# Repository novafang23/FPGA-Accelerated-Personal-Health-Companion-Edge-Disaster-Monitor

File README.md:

# SIH26181: VALOR (Vital and Atmospheric Logic for Offline Rescue)
### FPGA-Accelerated Personal Health Companion & Edge Disaster Monitor

An end-to-end heterogeneous edge System-on-Chip (SoC) pairing **synthesizable Verilog hardware acceleration** (Renesas ForgeFPGA & Xilinx Zynq-7000) with **dual-core ESP32-S3 FreeRTOS firmware** and an **on-device INT8 TinyML neural network**. Designed to operate 100% offline in communication-denied disaster environments, it delivers 20 ns cycle-accurate PPG jitter elimination, real-time mNEWS2 clinical triage, and multi-hazard environmental risk assessment (heatwaves, toxic smog, and floods).

---

## 🏷️ Platform Status & Roadmap

* **Verified Baseline:** [Xilinx Zynq-7000 (`xc7z020`)](hardware/zynq/) — Fully verified with 6/6 passing self-checking tests and static timing closed at 69.45 MHz (permanently tagged at `v1.0-zynq-SIH`).
* **Active Port:** [ShrikeFi (ESP32-S3 + Renesas ForgeFPGA)](hardware/shrikefi/) — Affordable edge hardware platform. Post-synthesis fitter reports **533 / 1120 LUT5s (47.59%)**, 367 FFs and 118/140 CLBs (84.29%) at **Fmax 77.712 MHz, WNS +7.131 ns** against the 50 MHz clock, with 13 passing self-checking link checks (5 groups). Raw synthesis logs: [`hardware/shrikefi/synthesis_evidence/`](hardware/shrikefi/synthesis_evidence/) (read its README — two older, superseded builds' numbers are also in there). Includes **fully integrated ESP32-S3 firmware** that streams live health telemetry via **USB UART & WiFi/MQTT**. (The firmware also programs the FPGA over **SPI2** at every boot using the Vicharak `Web_FPGA_programmer.ino` sequence; the boot log reaches `configuration COMPLETE! (46408 bytes loaded)` and the runtime link then answers its `0x55` probe, which is the real proof a configured design is running. See [`firmware/shrikefi/README.md`](firmware/shrikefi/README.md#fpga-delivery-how-the-bitstream-reaches-the-fpga).)
* **Clinical Intelligence & Biomarkers:** Fuses **mNEWS2 Clinical Triage (Royal College of Physicians)**, **PPG-derived Respiratory Rate (Charlton 2018)**, **Signal Quality Index (Elgendi 2016 skewness + project perfusion/IBI terms)**, **Moran's Physiological Strain Index (PSI)**, **PM2.5-HRV autonomic-strain heuristic (motivated by Brook et al. 2010)**, and the **published PMS5003 PM2.5 correction** (EPA/Barkjohn 2021 method, AirGradient's PMS5003 atm-channel equations) applied to a 60 s rolling mean.
* **Interactive Graphical Dashboard:** Standalone Windows desktop GUI (`shrikefi_dashboard.exe`) featuring a 60 FPS real-time optical PPG oscilloscope, live vital displays, and dual-mode operation (Live Hardware streaming + 6 simulated disaster profiles).

---

## 🔬 Reproducibility & Evidence Provenance

Every headline number below is reproducible from a committed command. Where a claim **cannot** be fully reproduced from this repository, that is stated explicitly rather than glossed over.

### Reproducible claims

| Claim | Reproduce with | Expected result |
|---|---|---|
| Zynq RTL — self-checking testbench | `hardware/zynq/build_and_run.bat` (or the `iverilog`/`vvp` pair it wraps) | `6 passed, 0 failed` |
| ShrikeFi RTL — SPI link testbench (`hardware/shrikefi/tb_forgefpga_system.v`) | `hardware/shrikefi/build_shrikefi_sim.bat` | `RESULTS: 13 passed, 0 failed (out of 13 checks)` |
| Firmware unit tests (incl. FP32↔INT8 parity) | `make -C firmware/zynq test` | `ALL TESTS PASSED.` |
| INT8 model regeneration | `python3 firmware/core/train_nn_risk_model.py` | `88.47%` FP32 / `88.39%` INT8 teacher agreement, `619` params, INT8 max error `0.091` |
| Clinical triage metrics | build & run `firmware/core/accuracy_evaluator.c` on `data/mimic/mimic_eval_feed.csv` | sensitivity `58.18%`, specificity `98.19%` (accuracy `94.11%`), TP `971` / FP `267` / TN `14451` / FN `698` |
| MIMIC cohort scan | build & run `firmware/core/mimic_harness.c` on `data/mimic/mimic_vital_feed.csv` | 16,387 records over 98 subjects |
| Zynq resource/timing reports | `hardware/zynq/synthesis_evidence/*.rpt` | see that directory's README |
| ForgeFPGA resource report | `hardware/shrikefi/synthesis_evidence/resource_utilization_spi_link_crest_2026-11-02.log` | 533/1120 LUT5s, 367 FFs, 118/140 CLBs (see that directory's README) |

CI (`.github/workflows/ci.yml`) runs the Zynq testbench, the ShrikeFi testbench, the firmware unit tests, and the accuracy evaluator, and fails the build if the model drops below its accuracy floor.

### Provenance caveats — read before quoting these numbers

1. **The RMSSD column in the MIMIC feeds is synthetic.** The HR and SpO₂ columns are genuine MIMIC-III `CHARTEVENTS` values (verified against the raw tables — e.g. subject 10013: SpO₂ min 60, HR max 113, 82 rows, matching the feed exactly). But **MIMIC-III v1.4 contains no waveform, ECG or numerics tables**, so beat-to-beat intervals — and therefore RMSSD — cannot be derived from it. The feed's RMSSD is generated: it has 16,384 distinct values across 16,387 rows over only 1,433 distinct (HR, SpO₂) pairs, i.e. essentially a unique float per row. Treat any metric that depends on RMSSD as *conditional on that synthetic input*.
2. **The dataset is the MIMIC-III demo subset** (98 subjects), not the full MIMIC-III cohort. It is a benchmark fixture, not an epidemiological result.
3. **`ground_truth_crisis` is derived in-tree.** No upstream generator script for those labels is committed, and the labels vary within a patient over time, consistent with a vitals-derived rule. The triage metrics are therefore best read as *agreement with that labeling rule*, not as independent clinical validation.
4. **The "88.39% accuracy" figure is agreement with a rule-based teacher**, not with clinical outcomes. `train_nn_risk_model.py` distils `disaster_risk_engine.c` into a 619-parameter network; both the training labels and the validation labels come from that same teacher.
5. **The 185 LUT / +5.603 ns Zynq figures are the tagged `v1.0-zynq-SIH` baseline.** Their only surviving in-repo evidence is the PNG screenshots; the raw report was overwritten when `.runs/` was regenerated under Vivado 2026.1. See [`hardware/zynq/synthesis_evidence/README.md`](hardware/zynq/synthesis_evidence/README.md) for which numbers belong to which run.
6. **ESP32-S3 inference latency is not measured.** The `0.44 µs` figure is an x86-64 host measurement. Do not quote it as a target-device number.

---

## 📌 Key Architectural Highlights

* **Cycle-Accurate Hardware Timing:** Dedicated 50 MHz FPGA timer measures heartbeat Inter-Beat Intervals (IBI) with **20 nanoseconds resolution**, eliminating the 5–20 ms operating system scheduling jitter that corrupts Heart Rate Variability (HRV).
* **Area-Optimized DSP Architecture:** Single 8-tap moving average filter implemented using an **$O(1)$ running-sum algorithm with wire-shift division (`>> 3`)**, requiring **0 DSP48 multiplier slices and 0 Block RAMs**.
* **Robust Bus Interfacing:** Standard ARM AMBA AXI4-Lite slave engine with **decoupled `AW` and `W` channel handshakes**, eliminating bus deadlocks on out-of-order interconnects. Includes **Write-1-to-Clear (W1C)** status registers to prevent interrupt race conditions.
* **High-Accuracy On-Device TinyML (INT8):** 2-hidden-layer micro-architecture ($6 \to 24 \to 16 \to 3$) requiring only **619 bytes** of parameter storage, reaching **88.39% agreement with the rule engine** on a 7,000-sample held-out synthetic validation set (88.47% for the float32 reference) (see [Reproducibility](#-reproducibility--evidence-provenance)) with **97.32% FP32↔INT8 tier agreement**, and executing in **0.44 µs per inference** (measured, `-O2`, x86-64 host; ESP32-S3 target timing not yet measured) with zero cloud dependencies.
* **Multi-Disaster Resilience (Tailored for India):**
  * *Heat Waves:* Fuses **NOAA Steadman Heat Index** and **Moran's Physiological Strain Index (PSI)** with cardiac tachycardia to warn of heat exhaustion before collapse.
  * *Smog Events:* Combines **published-correction PM2.5** (EPA/AirGradient banded equations on a 60 s mean, with a confidence code) with an **AHA-motivated PM2.5-HRV autonomic-strain heuristic** to flag acute vagal suppression ($RMSSD$ drop).
  * *Floods / Cold Shock:* Detects rapid skin cooling, cold-shock hyperventilation, and bradycardia.
* **Qualcomm Silicon Portability:** Prototyped on Xilinx Zynq-7000 and Renesas ForgeFPGA with a defined production migration roadmap to **Qualcomm Snapdragon Wear W5+ Gen 1** using **Hexagon™ Vector eXtensions (HVX)** on the Low-Power Island (< 5 mW) and **Qualcomm AI Engine (SNPE/QNN)**.

---

## 🏛️ System Architecture & End-to-End Data Flow

### 1. High-Level Dataflow Pipeline
The system operates across four coordinated processing tiers, moving from raw physical sensor acquisition to hardware-accelerated DSP, on-device TinyML inference, and local offline hazard advisory:

### 2. Heterogeneous Hardware / Firmware Architecture

```
┌──────────────────────────────────────────────────────────────────────────────────────────────────────┐
│                                       PHYSICAL SENSORS (I2C / UART)                                  │
│   • MAX30102 (Red 660nm / IR 940nm)    • BME280 (Temp / Humidity)    • PMS5003 (Laser PM2.5)         │
└──────────────────────────────────────────────────┬───────────────────────────────────────────────────┘
                                                   │
                                                   ▼
┌──────────────────────────────────────────────────────────────────────────────────────────────────────┐
│                              FPGA PROGRAMMABLE LOGIC (50 MHz RTL CORE)                              │
│                                                                                                      │
│   ┌───────────────────────────────────┐    8-Bit SPI (mode 0)  ┌──────────────────────────────────┐  │
│   │ Single 8-Tap Moving Avg Filter    │◄───────────────────────┤ Memory-Mapped Register Interface │  │
│   │ (O(1) Running Sum, 0 DSP Slices)  │                        │ 0x00: REG_RED_RAW                │  │
│   └─────────────────┬─────────────────┘                        │ 0x04: REG_RED_FILTERED           │  │
│                     │                                          │ 0x08: REG_IBI_CYCLES (20ns tick) │  │
│                     ▼                                          │ 0x0C: REG_STATUS_THRESH (W1C)    │  │
│   ┌───────────────────────────────────┐                        │ 0x10: REG_IR_RAW                 │  │
│   │ 4-State Systolic Peak Detector    │──────── irq_beat ─────▶│ 0x14: REG_IR_FILTERED            │  │
│   │ (250ms Refractory Blanking Window)│                        └──────────────────────────────────┘  │
│   └───────────────────────────────────┘                                                              │
└──────────────────────────────────────────────────┬───────────────────────────────────────────────────┘
                                                   │ Memory-Mapped I/O / Hardware Interrupt
                                                   ▼
┌──────────────────────────────────────────────────────────────────────────────────────────────────────┐
│                                  PROCESSING SYSTEM (ARM CORTEX-A9 / ESP32-S3)                        │
│                                                                                                      │
│   • driver_ppg.c          : Register-level hardware abstraction & IBI extraction                     │
│   • hrv_analysis.c        : 300-interval circular buffer computing RMSSD (vagal tone) and SDNN       │
│   • spo2_engine.c         : Beer-Lambert Ratio-of-Ratios SpO₂ calibration (R = (AC/DC)R / (AC/DC)IR) │
│   • nn_risk_model_int8.c  : 6→24→16→3 TinyML Neural Network, INT8, 0.44 µs/inference     │
│   • disaster_risk_engine.c: Multi-disaster scoring engine (CTSI Heat Strain & PRSI Pollution Index)  │
│   • ssd1306.c             : 128×64 OLED graphics driver & real-time offline advisory display         │
└──────────────────────────────────────────────────────────────────────────────────────────────────────┘
```

---

## ⚙️ FPGA Hardware Microarchitecture (Vendor-Agnostic Core)

### 1. Single 8-Tap Moving Average Filter (`moving_average_8tap.v`)
To eliminate optical baseline wandering and high-frequency motion artifacts from raw photoplethysmography (PPG) data, the accelerator implements a hardware moving-average FIR filter:

* **Difference Equation:**
  $$y[n] = y[n-1] + \frac{x[n] - x[n-8]}{8}$$
* **Zero DSP / Zero BRAM Implementation:** The filter maintains a running 11-bit sum in flip-flops. Division by 8 is synthesized as an instantaneous hardwired bit-shift (`>> 3`), requiring **zero hardware multipliers (0 DSP48)** and **zero Block RAM**.
* **Latency:** Deterministic single-cycle throughput on every `data_valid` strobe.

---

### 2. 4-State Systolic Peak Detector & Refractory FSM (`ppg_peak_detector.v`)
To extract precise beat-to-beat timing intervals without CPU overhead, a dedicated finite state machine tracks the pulse waveform morphology in hardware:

#### FSM State Machine Breakdown:
| State | Binary | Functional Description | Exit Condition |
|---|:---:|---|---|
| `STATE_ARMED` | `2'b00` | Baseline monitoring state; arming circuit waits for rising edge. | Sample value exceeds dynamic threshold (`sample_in >= threshold_reg`). |
| `STATE_RISING` | `2'b01` | Tracks ascending slope of the systolic pulse wave. | Local peak inflection detected (`sample_in < sample_prev`). |
| `STATE_PEAK_FOUND`| `2'b10` | Latching timestamp, pulsing `irq_beat` (1 cycle), and capturing 32-bit IBI cycle count. | Instantaneous single-cycle transition to refractory blanking. |
| `STATE_REFRACTORY`| `2'b11` | Blanking window counter (250 ms = 12,500,000 cycles @ 50 MHz) to prevent false triggers on dicrotic notches. | Timer countdown reaches zero (`refractory_cnt == 0`). |

* **Hardware IBI Counter:** Runs continuously on the 50 MHz clock domain, providing **20.000 ns per tick resolution** ($T_{\text{clk}} = 1 / 50\text{ MHz} = 20\text{ ns}$).

---

## 🧠 On-Device TinyML Neural Network Architecture

The intelligence layer features an ultra-compact 2-hidden-layer feedforward artificial neural network (ANN) designed specifically for resource-constrained edge microcontrollers and low-power DSPs:

```
                  ┌────────────────────────┐
                  │ 6 Biological &         │
                  │ Environmental Inputs   │
                  └───────────┬────────────┘
                              │
                              ▼
                  ┌────────────────────────┐
                  │ Hidden Layer 1         │
                  │ 24 Neurons (ReLU)      │
                  └───────────┬────────────┘
                              │
                              ▼
                  ┌────────────────────────┐
                  │ Hidden Layer 2         │
                  │ 16 Neurons (ReLU)      │
                  └───────────┬────────────┘
                              │
                              ▼
                  ┌────────────────────────┐
                  │ 3 Multi-Hazard Outputs │
                  │ Logistic Sigmoid       │
                  └────────────────────────┘
```

### Model Topology & Computational Footprint:
* **Input Layer (6 Features):**
  1. `HR` (Heart Rate in Beats Per Minute)
  2. `RMSSD` (Root Mean Square of Successive Differences in ms — Vagal HRV marker)
  3. `SpO2` (Blood Oxygen Saturation in %)
  4. `Ambient Temperature` (°C)
  5. `Relative Humidity` (%)
  6. `Particulate Matter PM2.5` ($\mu\text{g}/\text{m}^3$)
* **Hidden Layer 1 (24 Neurons):** Fully connected with Rectified Linear Unit ($\text{ReLU}(z) = \max(0, z)$) activations ($6 \times 24 = 144$ weights + 24 biases).
* **Hidden Layer 2 (16 Neurons):** Fully connected with ReLU activations ($24 \times 16 = 384$ weights + 16 biases).
* **Output Layer (3 Multi-Hazard Neurons):** Logistic Sigmoid ($\sigma(z) = \frac{1}{1 + e^{-z}}$) activations ($16 \times 3 = 48$ weights + 3 biases) producing independent risk probabilities:
  * **Neuron 1 — Heat Stroke Risk:** Detects cardiovascular drift under severe heat index conditions.
  * **Neuron 2 — Air Pollution Risk:** Assesses respiratory distress caused by hazardous particulate matter.
  * **Neuron 3 — Flood / Hypothermia Risk:** Evaluates cold exposure and immersion-induced bradycardia.
* **INT8 Quantization & Memory Footprint:** Per-tensor symmetric INT8 weight storage reduces total parameter storage to **619 bytes** (**576 MAC operations**), executing in **0.44 µs** per inference on an x86-64 host at `-O2` with zero cloud dependencies. Target-side (ESP32-S3) latency has **not** been measured. Note what "INT8" does and does not mean here: the *weights* are stored as signed 8-bit integers and the *activations* are requantized to uint8, but the multiply-accumulate runs in single-precision float on the ESP32-S3's FPU, because the kernel dequantizes the weights per layer. The INT8 format buys flash and RAM and reproducibility; it does not turn this kernel into an integer MAC unit.
* **Accuracy & Validation:**
  * **Synthetic Multi-Disaster Validation:** **88.47%** exact tier agreement for the float32 reference and **88.39%** for the deployed INT8 model (the artifact the firmware actually runs) on a **7,000-sample** held-out split of the synthetic scenario set (validation MSE `0.002979`, FP32↔INT8 tier agreement 97.32%). "Agreement" is agreement with the rule-based teacher the network was distilled from, not clinical accuracy. Reproduce with `python3 firmware/core/train_nn_risk_model.py`; CI enforces floors via `--min-accuracy` and `--min-int8-accuracy`.
  * **Clinical MIMIC-III ICU Database Benchmark:** **94.11%** triage accuracy over 16,387 MIMIC-III ICU time steps, with 58.18% sensitivity / 98.19% specificity. **The HR and SpO₂ inputs are real MIMIC-III chart events; the RMSSD column is synthetic**, because MIMIC-III v1.4 ships no waveform data from which beat-to-beat intervals could be derived. See [Reproducibility](#-reproducibility--evidence-provenance).

---

## 📈 Hardware Simulation & Waveform Timing Analysis

### 1. Cycle-Accurate GTKWave Timing Simulation (`tb_ppg_system.v`)
The GTKWave trace below demonstrates the decoupled ARM AMBA AXI4-Lite slave handshakes, the filtered analog pulse tracking, the single-cycle systolic interrupt pulse, and the latching of the 32-bit IBI cycle register:

#### Timing Trace Walkthrough:
* **Decoupled AXI Write:** Independent `AW` (Address Write) and `W` (Data Write) channels complete in separate clock cycles without stalling the master interconnect.
* **Filter Smoothing:** The raw digital input samples are smoothed by the running-sum pipeline into `filter_red_out[7:0]`.
* **Inflection Detection:** As the waveform rises past the threshold, the FSM transitions `ARMED` $\rightarrow$ `RISING` $\rightarrow$ `PEAK_FOUND`.
* **Hardware Interrupt (`irq_beat`):** A 1-cycle active-high pulse fires at cycle 68, latching the IBI cycle count `0x00000CD1` (3,281 ticks @ 50 MHz = 65.62 µs simulated interval).

---

### 2. Vivado Cycle-Accurate RTL Waveforms
Full functional verification of `tb_ppg_system.v` in AMD Xilinx Vivado ML (6/6 self-checking test vectors passing):

---

## 🔬 Vivado Post-Synthesis Static Timing & Utilization Evidence (Zynq Baseline)

### Baseline run — tagged `v1.0-zynq-SIH`

Synthesized Out-of-Context (OOC) with **AMD Xilinx Vivado ML v2022.2**, target part `xc7z020clg400-1` (Speed Grade -1, Slow Process Corner 85°C). This is the frozen hackathon-baseline result, permanently preserved at tag `v1.0-zynq-SIH`:

| Metric / Resource | Value | Chip Available (`xc7z020`) | Status / Utilization |
|:---|:---:|:---:|:---:|
| **Worst Negative Slack (WNS)** | **+5.603 ns** | — | **TIMING MET (Setup)** |
| **Worst Hold Slack (WHS)** | **+0.184 ns** | — | **TIMING MET (Hold)** |
| **Estimated Fmax** | **69.45 MHz** | 50.0 MHz target | **1.38× Safety Margin** |
| **Lookup Tables (LUT)** | **185** | 53,200 | **0.35%** |
| **LUTRAM** | **16** | 17,400 | **0.09%** |
| **Flip-Flops (FF)** | **266** | 106,400 | **0.25%** |
| **DSP48 Multiplier Slices** | **0** | 220 | **0.00% (Pure Logic)** |
| **Block RAM (BRAM)** | **0** | 140 | **0.00%** |

> **Evidence note:** the only in-repo evidence for this specific run is the
> screenshots below (`docs/images/timing_summary.png`,
> `utilization_percentage.png`). The raw `.rpt` for the tagged run was not
> preserved before `.runs/` was regenerated — see
> [`hardware/zynq/synthesis_evidence/README.md`](hardware/zynq/synthesis_evidence/README.md).

### Re-synthesis in this tree — Vivado v2026.1, Sep 2026

A later re-synthesis is what the `.runs/` tree in this repository actually contains, and its raw reports **are** committed as text evidence under [`hardware/zynq/synthesis_evidence/`](hardware/zynq/synthesis_evidence/):

| Measurement | Value | Tool / Scope |
|:---|:---:|:---|
| Accelerator OOC slice LUTs | **198** (182 logic + 16 LUTRAM) | Vivado v2026.1, `axi_ppg_accelerator` OOC |
| Accelerator OOC slice registers | **267** | Vivado v2026.1, `axi_ppg_accelerator` OOC |
| DSPs / BRAMs | **0 / 0** | both runs agree |
| Integrated post-route WNS / WHS | **+12.836 ns / +0.106 ns** (1,806 endpoints) | full `design_ZYNQ_wrapper` (PS7 + SmartConnect + accelerator), timing met |
| Integrated placed LUTs / FFs | 562 / 667 | full `design_ZYNQ_wrapper` |

These two runs measure different things and are **not** a regression of one another: the +5.603 ns figure is the standalone accelerator OOC, while +12.836 ns is the whole block design post-route. Do not quote them interchangeably.

### Detailed Vivado Synthesis Reports & Schematics:

#### Timing Summary Report (baseline run, +5.603 ns WNS Closure):

#### FPGA Fabric Utilization Breakdown (baseline run, 185 LUTs / 0 DSPs):

#### On-Chip Power Dissipation Summary:

#### Synthesized RTL Schematic (Gate-Level Netlist):

#### Device Floorplan & Placement:

---

## ⚡ ShrikeFi Hardware Platform (ESP32-S3 + Renesas ForgeFPGA)

To scale beyond expensive development kits to an accessible disaster monitor (projected <$20 at-scale bulk manufacturing BOM), the accelerator was ported to the **ShrikeFi** dual-chip platform.

### 1. Interconnect Architecture & Pin Mapping

> [!CAUTION]
> **3.3V LVCMOS Electrical Boundary Warning:** All ESP32-S3 and Renesas ForgeFPGA pins operate strictly at **3.3V logic levels**. Exceeding 3.3V will permanently destroy the ICs.

#### ESP32-S3 ↔ Renesas ForgeFPGA Link Pinout:
| ESP32-S3 GPIO | ForgeFPGA Pin | Signal Name | Direction | Description |
|:---:|:---:|:---|:---:|:---|
| **GPIO 10** | **PIN_17** | `spi_ss_n` (CS) | MCU $\rightarrow$ FPGA | Chip select, active low, toggled manually around each transaction |
| **GPIO 11** | **PIN_18** | `spi_mosi` | MCU $\rightarrow$ FPGA | SPI data out — the 8-bit optical sample |
| **GPIO 12** | **PIN_16** | `spi_sck` | MCU $\rightarrow$ FPGA | SPI clock (mode 0, MSB first) |
| **GPIO 13** | **PIN_19** (+ `PIN_19_OE`) | `spi_miso` | FPGA $\rightarrow$ MCU | SPI data in — `{beat_latched, filt_sample[6:0]}` |
| **GPIO 8** | — | `fpga_en` | MCU $\rightarrow$ FPGA | FPGA hardware enable |
| **GPIO 9** | — | `fpga_pwr` | MCU $\rightarrow$ FPGA | FPGA power control |
| — | **PIN_7** (+ `PIN_7_OE`) | `led_user` | FPGA $\rightarrow$ LED D12 | Blue user LED, flashed on each detected systolic crest |
| — | `OSC_EN` | `clk_en` | FPGA internal | Oscillator enable — the core has no clock unless this is driven |
| **GPIO 1/2** | — | `I2C SDA/SCL` | Bidirectional | Sensor bus (MAX30102, BME280, SSD1306 OLED) |
| **GPIO 14 (RX) / 18 (TX)** | — | `UART1` PMS5003 | Bidirectional | Laser particulate sensor (PM2.5) bus, 9600 8N1 |

The link is a 4-wire SPI bus (mode 0) with the ESP32-S3 as controller on `SPI2_HOST`; the ForgeFPGA is a bare fabric target with no processor and no AXI bus. **GPIO 3 / PIN_13 is not a reset pin and is not part of the interconnect** — nothing drives it; the ForgeFPGA resets itself from an internal power-on counter (`POR_CYC` in `forgefpga_ppg_top.v`). There is no strobe line, no direction line, no command codebook and no separate beat-interrupt pin: the beat arrives as bit 7 of the MISO byte. Authoritative sources: [`hardware/shrikefi/forgefpga_pins.pcf`](hardware/shrikefi/forgefpga_pins.pcf) and [`firmware/shrikefi/shrikefi_pinmap.h`](firmware/shrikefi/shrikefi_pinmap.h).

---

### 2. 8-Bit SPI Link Protocol Timing

The ShrikeFi board has no on-chip AXI bus and the ForgeFPGA has no processor, so the two chips exchange data over a plain 4-wire SPI bus. High-speed transactions are framed as a single byte, not as nibbles:

> The timing figure that used to sit here showed the retired 4-bit parallel
> protocol and has been removed rather than reproduced. The frame and timing are
> specified in [`docs/PROJECT_CONTEXT.md`](docs/PROJECT_CONTEXT.md);
> regenerate the figure from those tables before reuse.

* **Frame:** one 8-bit full-duplex transaction per optical sample, at roughly 100 Hz. CS (`GPIO 10` / `PIN_17`) is pulled low around the transaction; the MCU shifts the 8-bit sample out on MOSI while the FPGA shifts its reply back on MISO over the same 8 clock edges. The runtime link runs at 1 MHz; the bitstream is pushed over the same bus at 16 MHz during boot.
* **Returned Byte:** `{beat_latched, filt_sample[6:0]}` — **bit 7 is the beat flag**, bits 6:0 are the low 7 bits of the 8-tap moving average. There is no command map, no strobe and no separate interrupt line; the systolic crest simply sets bit 7 of the next MISO byte.
* **IBI Derivation:** the FPGA latches a 32-bit 50 MHz cycle count on each beat and queues a five-byte burst (`0xC3` + four bytes, MSB first). The MCU reads the count from that burst; only if the magic byte is absent (older bitstream) or the value is out of range does it fall back to `esp_timer_get_time()` deltas.

---

### 3. Renesas ForgeFPGA (`SLG47910C`) Post-Synthesis Resource Footprint

Post-synthesis compilation results from **Renesas ForgeFPGA Workshop v6.55** targeting the `SLG47910C` (1120 5-input LUTs):

* **Logic LUT5 Usage:** **533 / 1120 CLB LUT5s (47.59%)** — **52.41% of LUT fabric remains free**, but see the CLB row below: LUT headroom is not the real constraint.
* **Registers / Flip-Flops:** **303 Flip-Flops** (298 CLB FFs @ 26.61% + 5 IOB FFs @ 0.68%).
* **CLB Macrocells:** **118 / 140 Blocks (84.29%)** — CLB occupancy is the binding constraint and is nearly exhausted (**22 CLBs free**). The 2026-11-02 crest-timestamping change cost 13 CLBs for only 18 LUT5s, so assume any datapath widening needs a fitter run before claiming it fits. The SPI design runs from the on-chip oscillator, so the PLL is **free (0/1)**.
* **DSP Multipliers & BRAM:** **0 DSP Multipliers, 0 Block RAMs** (synthesized purely from logic).

> **Footnote — the 443-LUT figure quoted by older revisions of this file, the
> theory notes and the presentation decks belongs to the superseded 4-bit
> parallel-link build**, which was replaced by the SPI link in commit `a44013f`.
> It describes a different design, and its "only PLL is consumed" caveat no
> longer applies. Evidence and comparison:
> [`hardware/shrikefi/synthesis_evidence/README.md`](hardware/shrikefi/synthesis_evidence/README.md).
> The current numbers in this subsection are the 2026-10-18 burst fit; the fit
> history (including the pre-burst 362-LUT figure) is in the evidence README.

#### ForgeFPGA Workshop GUI Synthesis Evidence:

#### Synthesized SLG47910C Macrocell Top-Level Core Schematic:

#### Device Floorplan & Block Placement:

#### RTL Simulation Waveform (PPG Peak Detection)

The waveform above validates the hardware-accelerated PPG systolic peak detection algorithm executing on the ShrikeFi FPGA. Key observations from the simulation:
* **Digital Filtering:** The raw PPG input (`reg_red_raw`) is processed by the hardware filter to yield a smoother `red_filtered` signal.
* **Adaptive Thresholding & State Machine:** As the filtered signal crosses the dynamic `reg_threshold`, the FSM (`current_state`) transitions appropriately to identify the systolic crest.
* **Beat Detection & IBI Latching:** Upon confirming a valid peak, the system fires a single-cycle `peak_beat_detected` pulse. Simultaneously, the `peak_ibi_cycles` register latches the precise cycle count (e.g., `3279` cycles) to determine the Inter-Beat Interval (IBI), and the `interval_cnt` is reset for the subsequent beat.

---

## 📐 Performance Measurement & Benchmarking Methodology

To ensure transparent, reproducible engineering rigor, all performance metrics are derived as follows:

### 1. Maximum Frequency ($F_{\text{max}} = 69.45\text{ MHz}$) Calculation
* **Tool:** AMD Xilinx Vivado ML v2022.2 (Out-of-Context Synthesis & Static Timing Analysis).
* **Target Part:** `xc7z020clg400-1` (Speed Grade -1, Slow Process Corner at 85°C).
* **Derivation Formula:**
  $$T_{\text{critical}} = T_{\text{clk}} - \text{WNS} = 20.000\text{ ns} - 5.603\text{ ns} = 14.397\text{ ns}$$
  $$F_{\text{max}} = \frac{1}{T_{\text{critical}}} = \frac{1}{14.397\text{ ns}} \approx \mathbf{69.45\text{ MHz}}$$
* **Critical Path:** Source register `peak_det_inst/sample_prev_reg[6]/C` $\rightarrow$ 4 logic levels (LUT2 $\rightarrow$ LUT4 $\rightarrow$ LUT4 $\rightarrow$ LUT6) $\rightarrow$ Destination register `peak_det_inst/ibi_counter_reg[22]/D`.

### 2. TinyML Inference Latency ($0.44\ \mu\text{s}$, measured on an x86-64 host)
* **Model Profile (shipped INT8 model, $6 \to 24 \to 16 \to 3$):** 619 INT8 parameters/bytes — 576 weights ($144 + 384 + 48$) plus 43 biases ($24 + 16 + 3$) — and therefore **576 INT8 Multiply-Accumulate (MAC) operations**, plus 40 ReLU comparisons (24 + 16) and 3 Sigmoid evaluations.
* **Op-Count Breakdown:**
  * Layer 1 (Hidden 24): $6 \times 24 = 144\text{ MACs}$ + 24 ReLU.
  * Layer 2 (Hidden 16): $24 \times 16 = 384\text{ MACs}$ + 16 ReLU.
  * Layer 3 (Output 3): $16 \times 3 = 48\text{ MACs}$ + 3 Sigmoid.
  * **Total: $576\text{ MACs} + 40\text{ ReLU} + 3\text{ Sigmoid}$ over 619 bytes of parameters.**
* **Measured Latency:** **0.44 µs per inference**, measured at `-O2` on an **x86-64 host**. This is a host figure and not an ESP32-S3 figure: the target MCU runs at 160 MHz (`CONFIG_ESP_DEFAULT_CPU_FREQ_MHZ=160`), and **target-side latency has not been measured**. Do not quote 0.44 µs as an ESP32-S3 number.

### 3. FPGA Inter-Beat Interval (IBI) Resolution ($20\text{ ns}$)
* **System Clock:** $f = 50.000\text{ MHz} \implies T = \frac{1}{f} = \mathbf{20.000\text{ ns per tick}}$.
* **32-Bit Counter Range:** $2^{32} \times 20\text{ ns} \approx 85.89\text{ seconds}$ (enables measuring heart rates from 0.7 BPM to 240 BPM without counter overflow).

---

## 💻 Live Console Demonstration Output (`main_simulation.c`)

Running `./health_demo.exe` executes real-time multi-sensor fusion and TinyML risk classification across simulated disaster profiles. The block below is **verbatim output** from the current binary (ANSI colour codes stripped, trimmed after the AI score panel); the console then cycles through the remaining disaster profiles:

```text
+================================================================+
|    SIH26181 Health Companion Simulator                         |
+================================================================+
 Scenario: Normal Resting (Indoor, 25C)  |  Time: 0s

 +---------------- VITALS -----------------+
 |  Heart Rate:    72.0    BPM              |
 |  SpO2:          98.0    %                |
 |  HRV RMSSD:     44.6    ms               |
 |  HRV SDNN:      30.7    ms               |
 +-----------------------------------------+

 +------------- ENVIRONMENT ---------------+
 |  Ambient Temp:  25.0    C                |
 |  Skin Temp:     36.5    C                |
 |  Humidity:      45.0    %                |
 |  PM2.5:         15      ug/m3            |
 +-----------------------------------------+

 +----------- RISK ASSESSMENT -------------+
 |  Heat Risk:       NORMAL                 |
 |  Pollution Risk:  NORMAL                 |
 |  Flood/Cold Risk: NORMAL                 |
 |                                         |
 |  >> OVERALL:      NORMAL                 |
 +-----------------------------------------+

 +--------- AI CONFIDENCE SCORES ----------+
 |  Heat Neuron:     0.000                  |
 |  Pollution Neuron:0.000                  |
 +-----------------------------------------+
```

> RMSSD/SDNN values above vary between runs with the simulated sensor noise; the scenario, vitals layout and risk lines are stable.

### Compare Harness: Rule Engine vs Neural Network Validation (`compare_harness.c`)

Running `./compare_harness.exe` tests the trained NN against the rule-based scoring engine across all 4 canonical scenarios:

```text
Scenario                  | RuleHeat  RulePoll  RuleFlood | NN-Heat   NN-Poll   NN-Flood 
--------------------------------------------------------------------------------
Normal Resting            | NORMAL    NORMAL    NORMAL    | 0.025     0.026     0.043    
Heat Wave (Delhi 47C)     | CRITICAL  NORMAL    MODERATE  | 0.835     0.124     0.248    
Severe Smog (AQI500+)     | NORMAL    CRITICAL  MODERATE  | 0.012     0.922     0.228    
Flash Flood/Hypothermia   | NORMAL    NORMAL    CRITICAL  | 0.008     0.112     0.500    
```

The NN correctly identifies the **dominant risk axis** in every scenario. Measured on the 7,000-sample held-out split against the rule-based teacher: **r = 0.99 (heat), r = 0.98 (pollution), r = 0.97 (flood)** for the deployed INT8 model, with **86.0–92.0%** exact risk-band agreement per axis (88.39% overall). See [`train_nn_risk_model.py`](firmware/core/train_nn_risk_model.py) for the full training script.

---

## 🗺️ Memory-Mapped Register Map (Zynq AXI4-Lite)

Base Address: `0x43C00000` (AXI4-Lite)

| Offset | Register Name | Access | Reset | Description |
|:---:|:---|:---:|:---:|:---|
| `0x00` | `REG_RED_RAW` | R/W | `0x00000000` | `[7:0]` Red PPG sample input (triggers filter pipeline) |
| `0x04` | `REG_RED_FILTERED` | RO | `0x00000000` | `[7:0]` Smoothed Red output (read by SpO₂ engine) |
| `0x08` | `REG_IBI_CYCLES` | RO | `0x00000000` | `[31:0]` Inter-Beat Interval in 20 ns clock ticks |
| `0x0C` | `REG_STATUS_THRESH`| Mixed| `0x00007800` | `[0]` `beat_flag` (W1C), `[15:8]` Systolic threshold (Default: 120) |
| `0x10` | `REG_IR_RAW` | R/W | `0x00000000` | `[7:0]` IR PPG sample input (triggers filter pipeline) |
| `0x14` | `REG_IR_FILTERED` | RO | `0x00000000` | `[7:0]` Smoothed IR output (read by SpO₂ engine) |

---

## ⚠️ Scientific Limitations & Validation Scope

To maintain transparent, professional engineering rigor, our validation boundaries are defined below:

1. **Hardware Implementation Scope:**  
   * The digital RTL is verified via cycle-accurate Icarus Verilog simulation (`tb_ppg_system.v`, 6/6 tests passing) and synthesized Out-of-Context (OOC) in Vivado ML targeting the `xc7z020` FPGA, and in Renesas ForgeFPGA Workshop targeting `SLG47910C`.
   * Physical silicon deployment targets Qualcomm Snapdragon Wear W5+ Gen 1 as an architectural migration mapping, alongside an active low-cost edge port to ShrikeFi (ESP32-S3 + Renesas ForgeFPGA).
2. **Medical & Physiological Modeling:**  
   * The 15–30 minute early warning window is a theoretical model estimate based on published clinical literature on *Cardiovascular Drift* (gradual upward drift in heart rate accompanied by progressive decline in stroke volume during prolonged thermal stress).
   * **Clinical Disclaimer:** This system is an edge disaster resilience prototype and is **not certified as a diagnostic medical device** under CDSCO/FDA regulations. Clinical deployment would require human subject trial validation.
3. **Sensor Emulation:**  
   * Sensor drivers (`max30102.c`, `bme280.c`, `pms5003.c`) contain physical register maps and a built-in PC simulation layer for functional validation against synthetic physiological waveforms.

---

## 📚 Scientific References & Literature Grounding

1. **Cardiovascular Drift:** Montain, S. J., & Coyle, E. F. (1992). *"Influence of graded dehydration on hyperthermia and cardiovascular drift during exercise."* *Journal of Applied Physiology*, 73(4), 1340-1350.
2. **Heart Rate Variability Standards:** Task Force of the European Society of Cardiology and the North American Society of Pacing and Electrophysiology (1996). *"Heart rate variability: standards of measurement, physiological interpretation and clinical use."* *Circulation*, 93(5), 1043-1065.
3. **Heat Index Assessment:** Steadman, R. G. (1979). *"The assessment of sultriness. Part I: A temperature-humidity index based on human physiology and evaporative science."* *Journal of Applied Meteorology and Climatology*, 18(7), 861-873. The firmware implements the NWS operational Rothfusz regression with its low-/high-humidity adjustments.

---

## 🎯 Qualcomm Silicon Migration Path

| Prototype Block (Zynq) | Qualcomm Production Subsystem | Migration Path & Benefit |
|:---|:---|:---|
| **Verilog Filter (`moving_average_8tap.v`)** | **Qualcomm Hexagon™ DSP + HVX** | Vectorized SIMD sliding-window filtering on Low-Power Island (< 1 mW). |
| **Peak FSM (`ppg_peak_detector.v`)** | **Qualcomm Sensor Core Hardware Timer** | 64-bit microsecond timestamp counter for jitter-free 24/7 cardiac monitoring. |
| **TinyML Model (`nn_risk_model.c`)** | **Qualcomm AI Engine (Hexagon NPU)** | Quantized to INT8 `.dlc` via SNPE/QNN SDK (< 100 ns inference, < 0.1 mJ). |
| **Sensors Drivers (`max30102.c`, etc.)** | **Qualcomm Universal Peripheral (QUP v3)** | DMA transfer via Bus Access Manager (BAM) with zero CPU wakeups. |
| **AMBA AXI4-Lite Interface** | **Qualcomm System Network-on-Chip (NoC)** | Native AMBA standard memory-mapped interoperability. |

---

## 📖 Master Theory Guide & Judge Defense Notes

---

## 📁 Repository Directory Structure

```
.
├── hardware/
│   ├── common/                     # Vendor-agnostic synthesizable Verilog RTL
│   │   ├── moving_average_8tap.v   # O(1) running-sum 8-tap digital noise filter (0 DSP)
│   │   ├── ppg_peak_detector.v     # 4-state systolic FSM with 250ms refractory timer
│   │   └── tb_ppg_peak_detector.v  # Unit testbench for peak detector
│   ├── zynq/                       # Xilinx Zynq-7000 baseline implementation
│   │   ├── axi_ppg_accelerator.v   # Top-level AXI4-Lite slave wrapper & DSP top
│   │   ├── tb_ppg_system.v         # Self-checking AXI testbench (6/6 passing)
│   │   ├── ppg_accelerator.xdc     # Vivado Static Timing constraints (50 MHz)
│   │   ├── run_vivado_synth.tcl    # Automated Vivado batch synthesis script
│   │   ├── signals.gtkw            # Color-coded GTKWave waveform layout
│   │   └── build_and_run.bat       # Interactive one-click launcher for Zynq flow
│   ├── shrikefi/                   # Active port target (ESP32-S3 + Renesas ForgeFPGA)
│   │   ├── pcb/                    # Complete KiCad schematic, PCB layout & BOM
│   │   │   ├── shrikefi_werable.kicad_pcb
│   │   │   ├── shrikefi_werable.kicad_sch
│   │   │   └── SIH26181_ShrikeFi_Wearable_BOM.csv
│   │   ├── forgefpga_ppg_top.v     # SPI target + shared DSP wrapper (filter/detector come from common/)
│   │   ├── tb_forgefpga_system.v   # Self-checking SPI link testbench (5 groups / 13 checks)
│   │   └── forgefpga_pins.pcf      # Renesas ForgeFPGA physical pin constraints
│   └── cad/                        # 3D Enclosure CAD drawings, renders & reports
│       ├── SIH26181_Hardware_Integration_CAD_Design_Report.pdf
│       ├── exploded_cad_assembly.jpg
│       ├── cad_orthographic_drawing.jpg
│       └── fusion360_wearable_cad.jpg
│
├── firmware/
│   ├── core/                       # Platform-agnostic clinical algorithms & TinyML inference
│   │   ├── clinical_vitals_engine.c # Royal College of Physicians mNEWS2 Early Warning System
│   │   ├── ppg_sqi.c / .h          # Elgendi 2016 skewness-based SQI (+ project terms)
│   │   ├── ppg_respiratory_rate.c  # Addison & Charlton PPG-derived Respiratory Rate
│   │   ├── hrv_analysis.c / .h     # RMSSD & SDNN circular buffer mathematics
│   │   ├── spo2_engine.c / .h      # Ratio-of-ratios pulse oximetry calculation
│   │   ├── disaster_risk_engine.c  # Moran PSI, Steadman/Rothfusz HI, PM2.5-HRV heuristic, project-trained PM2.5 NN
│   │   ├── nn_risk_model.c / .h    # Float32 feedforward TinyML model (6→24→16→3)
│   │   ├── nn_risk_model_int8.c    # INT8 Quantized TinyML engine (619 bytes SRAM, 88.39% teacher agreement)
│   │   ├── accuracy_evaluator.c    # MIMIC-III triage metrics (94.11% acc / 58.18% sens, confusion matrix)
│   │   └── mimic_harness.c         # MIMIC-III cohort scan (triage level counts + latency only)
│   ├── zynq/                       # Zynq PS application, sensor drivers & harnesses
│   │   ├── main_simulation.c       # Interactive multi-disaster console demo
│   │   ├── compare_harness.c       # Rule Engine vs TinyML validation harness
│   │   ├── test_disaster_risk_engine.c # Comprehensive firmware unit test suite
│   │   ├── driver_ppg.c / .h       # Register-level hardware abstraction layer
│   │   ├── max30102.c / .h         # Dual-wavelength optical PPG sensor driver
│   │   ├── bme280.c / .h           # Bosch environmental sensor driver (T, H, P)
│   │   ├── pms5003.c / .h          # Laser particulate sensor UART driver (PM2.5)
│   │   ├── ssd1306.c / .h          # 128×64 OLED graphics driver
│   │   └── Makefile                # Native makefile for firmware build
│   └── shrikefi/                   # ESP-IDF / FreeRTOS firmware implementation
│       ├── main_shrikefi.c         # Dual-core FreeRTOS biometric & hazard tasks
│       ├── shrikefi_dashboard.c    # Standalone Win32 GDI real-time GUI dashboard
│       ├── max30102.c / .h         # Auto-sensing MAX30100 & MAX30102 driver
│       ├── pms5003.c / .h          # Plantower laser particulate PM2.5 UART driver
│       ├── shrikefi_link_driver.c  # Full-duplex SPI2 link driver & bitstream programmer
│       ├── wifi_mqtt_manager.c     # ESP-IDF WiFi connectivity & MQTT cloud sync
│       ├── forgefpga_bitstream.h   # Auto-generated C header of the ForgeFPGA bitstream
│       ├── CMakeLists.txt          # ESP-IDF component build configuration
│       ├── build_and_flash.bat     # One-click ESP-IDF build + flash + monitor
│       └── run_dashboard.bat       # GUI dashboard launcher
│
├── data/
│   └── mimic/                      # MIMIC-III benchmark validation dataset
│       ├── mimic_vital_feed.csv    # 16,387 MIMIC-III ICU rows (real HR/SpO2, synthetic RMSSD)
│       └── mimic_eval_feed.csv     # Multi-hazard ground truth labels
│
├── reports/                        # DeepSeek clinical audits & MIMIC-III benchmark logs
│   ├── CLINICAL_AI_ACCURACY_REPORT.md
│   ├── DEEPSEEK_AUDIT_VERIFICATION_PASSED.md
│   ├── DEEPSEEK_CLINICAL_PAPERS_OPINION.md
│   └── FINAL_A_TO_Z_SYSTEM_AUDIT_REPORT.md
│
├── scripts/                        # Automation & copilot utilities
│   ├── deepseek_copilot.py         # AI clinical co-pilot reasoning script
│   ├── deepseek.bat                # Copilot CLI shortcut
│   ├── valor_code_auditor.py       # Antigravity SDK multi-agent code auditor
│   ├── generate_sih_presentation.py # Widescreen pitch presentation generator
│   └── generate_sih_official_presentation.py # Official SIH template generator (6 slides)
│
├── docs/
│   ├── PROJECT_CONTEXT.md          # ← complete A→Z context (start here)
│   ├── VALOR_WEARABLE_PCB_DESIGN_GUIDE.md  # wearable PCB design intent (Rev A)
│   ├── reference/                  # original Vicharak ShrikeFi pinouts & reference code
│   │   └── shrike_board/           # shrike_pinouts_full.txt, Web_FPGA_programmer.ino, ...
│   └── images/                     # schematic / diagram exports (SVG)
│
├── .github/workflows/              # CI: compilation, testing, secret scanning
├── launch_dashboard.bat            # One-click native desktop GUI launcher
├── run.bat                         # Top-level interactive Windows launcher
├── CONTRIBUTING.md                 # Contribution guidelines
├── ROADMAP.md                      # Project roadmap & milestones
├── README.md                       # Main repository landing page
├── LICENSE                         # MIT License
└── .gitignore                      # Git artifact exclusion rules
```

---

## 🖥️ Dashboards

### VALOR Web Dashboard (recommended for demos)

A single self-contained HTML file: **no install, no build step, no server, no CDN.**
Open it in Chrome or Edge and press *Connect* — Web Serial talks to the ESP32-S3
over USB directly. With no board attached it runs the six clinical profiles, so a
demo never depends on hardware.

Double-click **`launch_web_dashboard.bat`**, or open
`firmware/shrikefi/dashboard/valor_dashboard.html` yourself.
See [`firmware/shrikefi/dashboard/README.md`](firmware/shrikefi/dashboard/README.md).

**Nothing is shown until you choose.** The dashboard opens in an *idle* state — every
readout blank — and fills in only once you connect a device or explicitly start a
simulation. An unconnected dashboard showing a plausible heart rate would be worse
than one showing nothing.

| Normal baseline | Heat wave & dehydration | Cardiopulmonary ICU emergency |
|---|---|---|

*Live optical PPG scope with sweep and glow, mNEWS2 triage, per-vital cards, environmental panel, and the INT8 multi-hazard gauges.*

> **Why it exists alongside the native app:** the design language is web-native —
> glass cards, neon glow, gradient area fills, canvas animation. GDI has no
> equivalent, so this is additive rather than a rewrite. The `.exe` below still
> builds and still works.

> **Honest by construction.** The web dashboard computes **no clinical logic** — it
> renders what the device sends as `[TRIAGE]`, so the ESP32 stays the single
> source of truth. Several plausible-looking numbers from the original design
> mock-up were removed rather than shipped: no blood-pressure estimate, no PTT,
> NEWS2 sub-scores for parameters this build does not instrument are shown as
> `n/a` rather than `+0`, and the PM2.5-HRV strain (heuristic) is shown on its 0-1 scale. The
> full list is in the dashboard README.

---

### Native Win32 Dashboard (alternative)

The companion includes a high-performance, native Windows desktop GUI application (`shrikefi_dashboard.exe`) written in pure C using Win32 GDI graphics (0 external runtime dependencies, 60 FPS refresh rate):

### Key Dashboard Capabilities:
* **Dual-Mode Operation:**
  * **LIVE HARDWARE STREAMING (COM Port):** Auto-detects and connects to the ESP32-S3 USB COM port at 115,200 baud, plotting live optical PPG waveforms, heart rate, SpO2, and PM2.5 in real-time.
  * **OFFLINE DISASTER SIMULATOR:** Built-in multi-hazard simulation generator cycling across 6 clinical/disaster scenarios (Normal Baseline, Heat Wave & Dehydration, Severe Smog / PM2.5 Crisis, Flash Flood / Hypothermia, Cardiopulmonary ICU Emergency, Motion Artifact / Noise Test). The same six profiles drive the web dashboard, so both simulations present the same patient.
* **Real-Time Visual Oscilloscope:** 60 FPS scrolling sweep of filtered PPG systolic pulses with beat-to-beat cadence.
* **Full Biomarker Telemetry Panel:** Real-time digital readouts for Heart Rate, SpO2, Respiratory Rate, RMSSD HRV, Ambient Temperature, Relative Humidity, PM2.5, and Signal Quality Index (Elgendi-style SQI).
* **Clinical Triage & Hazard Meters:** Live color-coded gauges for **Royal College of Physicians mNEWS2 Triage** (NORMAL / ELEVATED / HIGH / CRITICAL) alongside the **INT8 TinyML Hazard Inference Engine** (Heatstroke, Smog, Hypothermia).
* **Instant Launch:** Simply double-click `launch_dashboard.bat` from the root directory.

---

## 🚀 Quickstart: Build & Run in 10 Seconds

### Prerequisites
* **Verilog Simulator:** Icarus Verilog (`iverilog` & `vvp`)
* **Waveform Viewer:** GTKWave
* **C Compiler:** GCC / MinGW (`gcc`)
* **Python (Optional):** Python 3.8+ (for ML scripts and linting)

### One-Click GUI Dashboard (Windows)
```cmd
# Launch the real-time 60 FPS graphical dashboard (Live Hardware COM / Disaster Simulator):
.\launch_dashboard.bat
```

### One-Click Menu Launcher (Windows)
```cmd
# Run interactive compilation, simulation, and real-time C console dashboard:
.\run.bat
```
The interactive menu allows you to launch the simulation, view waveforms, compare the Rule Engine vs NN, and run unit tests.

### Execution (Linux / Terminal)
```bash
# 1. Run RTL testbench simulation:
iverilog -o sim_ppg.vvp hardware/zynq/tb_ppg_system.v hardware/zynq/axi_ppg_accelerator.v hardware/common/moving_average_8tap.v hardware/common/ppg_peak_detector.v
vvp sim_ppg.vvp

# 2. Compile and run health simulation dashboard:
gcc -Wall -Wextra -Ifirmware/core -Ifirmware/zynq -o health_demo firmware/zynq/main_simulation.c firmware/core/hrv_analysis.c firmware/core/spo2_engine.c firmware/core/disaster_risk_engine.c firmware/core/clinical_vitals_engine.c firmware/core/ppg_sqi.c firmware/core/ppg_respiratory_rate.c firmware/core/nn_risk_model.c firmware/core/nn_risk_model_int8.c -lm
./health_demo

# 3. Compile and run unit tests:
gcc -Wall -Wextra -std=c11 -Ifirmware/core -Ifirmware/zynq -Ifirmware/shrikefi -o test_engine firmware/zynq/test_disaster_risk_engine.c firmware/core/hrv_analysis.c firmware/core/spo2_engine.c firmware/core/disaster_risk_engine.c firmware/core/nn_risk_model.c firmware/core/nn_risk_model_int8.c firmware/core/clinical_vitals_engine.c firmware/core/ppg_sqi.c firmware/core/ppg_respiratory_rate.c firmware/core/pm25_correction.c firmware/core/pressure_trend.c firmware/shrikefi/sos.c firmware/shrikefi/web_status.c firmware/shrikefi/location.c -lm
./test_engine
```

---

## 📊 Waveform Viewing (GTKWave)

Pre-configured presentation views for both platforms:

| Platform | Waveform File | Config File | Tests |
|----------|---------------|-------------|-------|
| **Zynq-7000** | `ppg_system.vcd` | `hardware/zynq/presentation.gtkw` | 6/6 passing |
| **ShrikeFi** | `hardware/shrikefi/shrikefi_sim.vcd` | `hardware/shrikefi/presentation.gtkw` | 13 checks passing |

### Quick Start
```bash
# Zynq-7000 (verified baseline)
gtkwave ppg_system.vcd hardware/zynq/presentation.gtkw

# ShrikeFi (ForgeFPGA + ESP32-S3)
gtkwave hardware/shrikefi/shrikefi_sim.vcd hardware/shrikefi/presentation.gtkw
```

### What You'll See
- **Zynq**: AXI4-Lite register transactions, dual 8-tap moving average filters (0 DSP/0 BRAM), 4-state peak detector FSM, beat interrupt + IBI cycles (20 ns resolution)
- **ShrikeFi**: 8-bit SPI FPGA↔MCU link (mode 0, one byte per sample), same filter/peak detector RTL, beat flag in bit 7 of the MISO byte, IBI derived on the MCU

For the commands that reproduce each waveform and test result, see [Reproducibility & Evidence Provenance](#-reproducibility--evidence-provenance)..

---

## 🤝 Contributing
We welcome issues and pull requests! Please see our CONTRIBUTING.md for guidelines on code formatting, running unit tests locally, and how to submit a PR.

---

## 📄 License & Attribution

Developed for the **Qualcomm Hardware Challenge — Smart India Hackathon 2026**.  
All Verilog RTL, C drivers, and documentation are provided under the [MIT License](LICENSE).

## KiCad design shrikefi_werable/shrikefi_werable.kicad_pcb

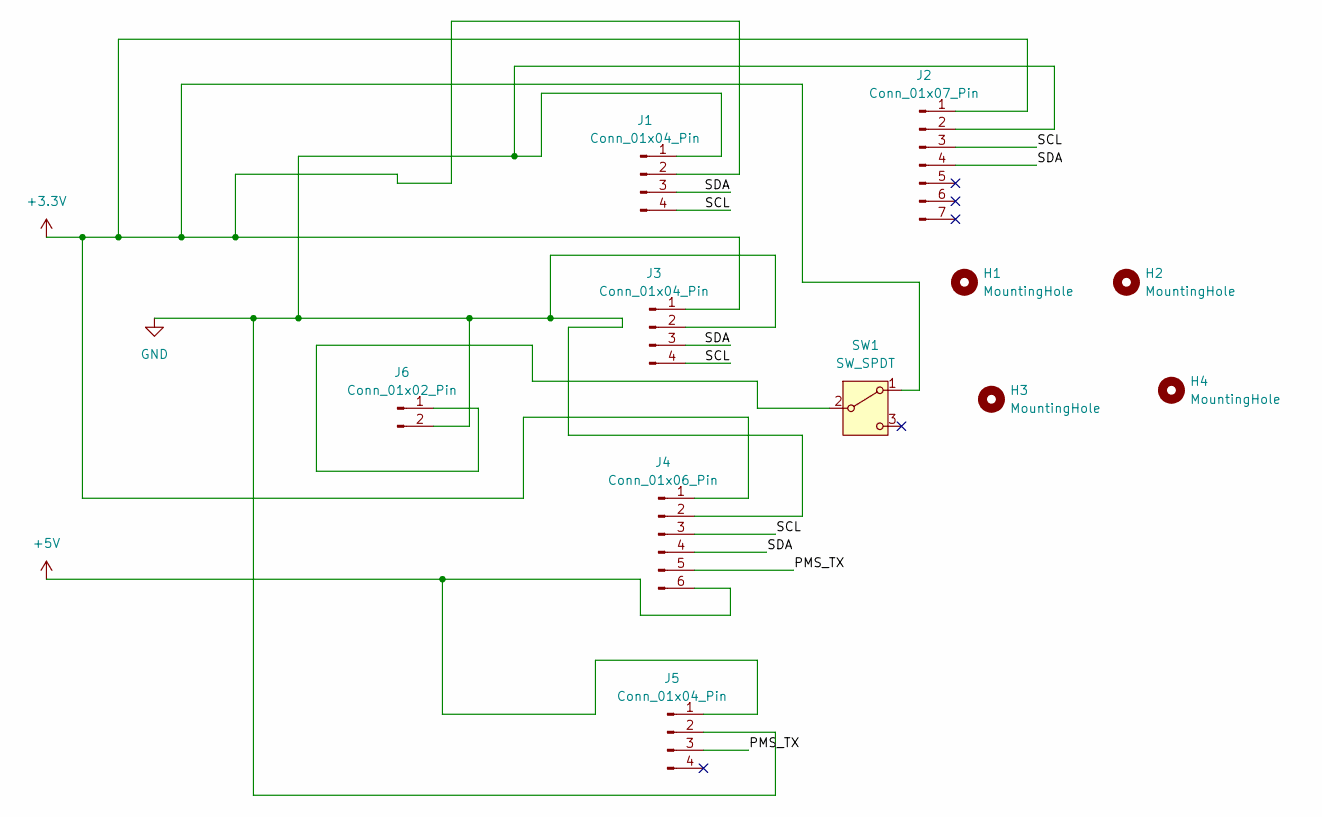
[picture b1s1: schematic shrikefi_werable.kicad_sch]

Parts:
H1, H2, H3, H4: MountingHole; MountingHole_2.2mm_M2
J1, J3, J5: Conn_01x04_Pin; FanPinHeader_1x04_P2.54mm_Vertical
J2: Conn_01x07_Pin; PinHeader_1x07_P2.54mm_Vertical
J4: Conn_01x06_Pin; PinHeader_1x06_P2.54mm_Vertical
J6: Conn_01x02_Pin; PinHeader_1x02_P2.54mm_Vertical
SW1: SW_SPDT; PinHeader_1x03_P2.54mm_Vertical

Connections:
+3.3V: J1.2, J2.1, J3.1, J4.1, SW1.1 (A)
+5V: J4.6, J5.1
/PMS_TX: J4.5, J5.3
/SCL: J1.4, J2.3, J3.4, J4.3
/SDA: J1.3, J2.4, J3.3, J4.4
GND: J1.1, J2.2, J3.2, J4.2, J5.2, J6.2
unnamed: J6.1, SW1.2 (B)

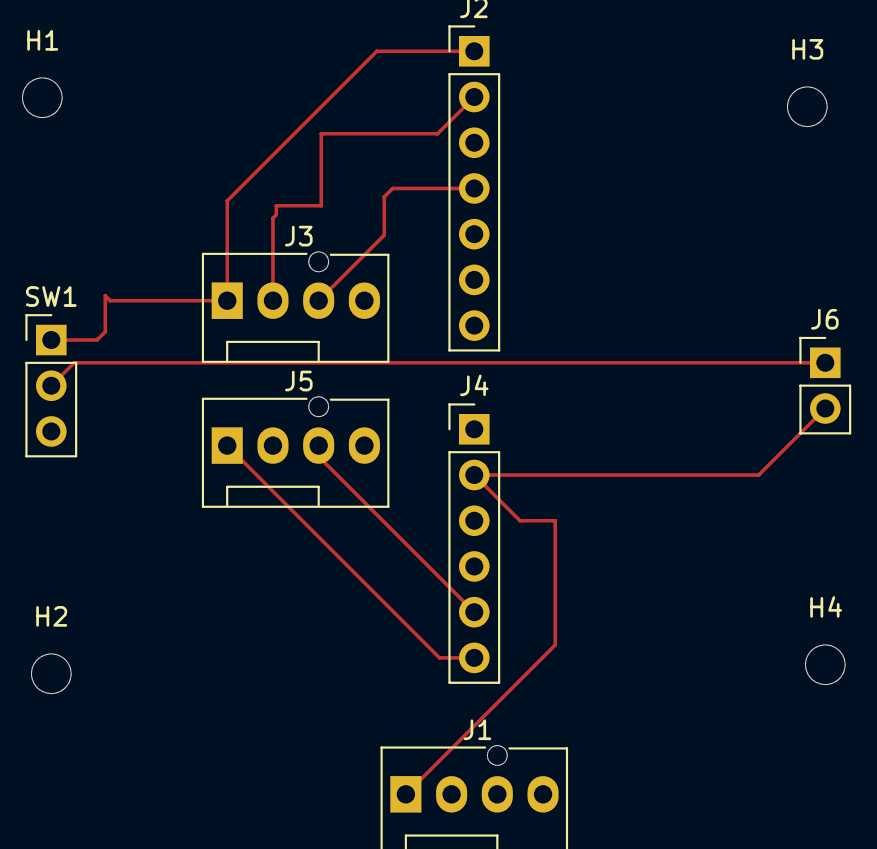
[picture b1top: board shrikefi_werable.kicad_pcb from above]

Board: 2 copper layers, 11 parts (0 on the bottom side), 7 nets.
